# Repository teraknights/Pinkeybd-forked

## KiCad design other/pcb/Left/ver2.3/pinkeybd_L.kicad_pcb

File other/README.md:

# Pinkeybd
"Pinkeybd" is a portable wireless split keyboard with trackball

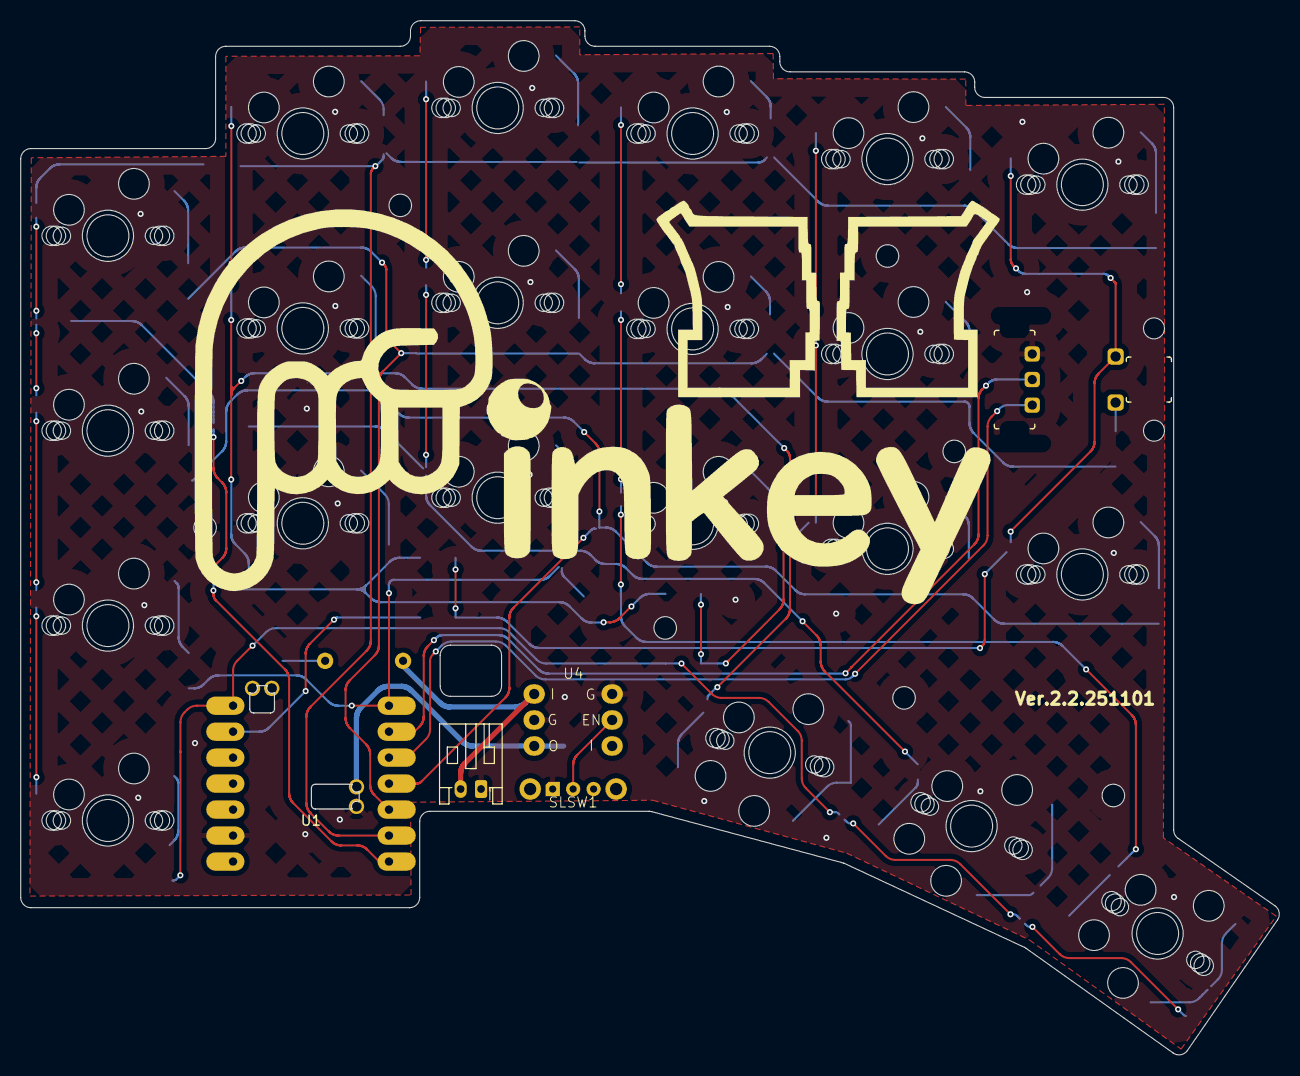
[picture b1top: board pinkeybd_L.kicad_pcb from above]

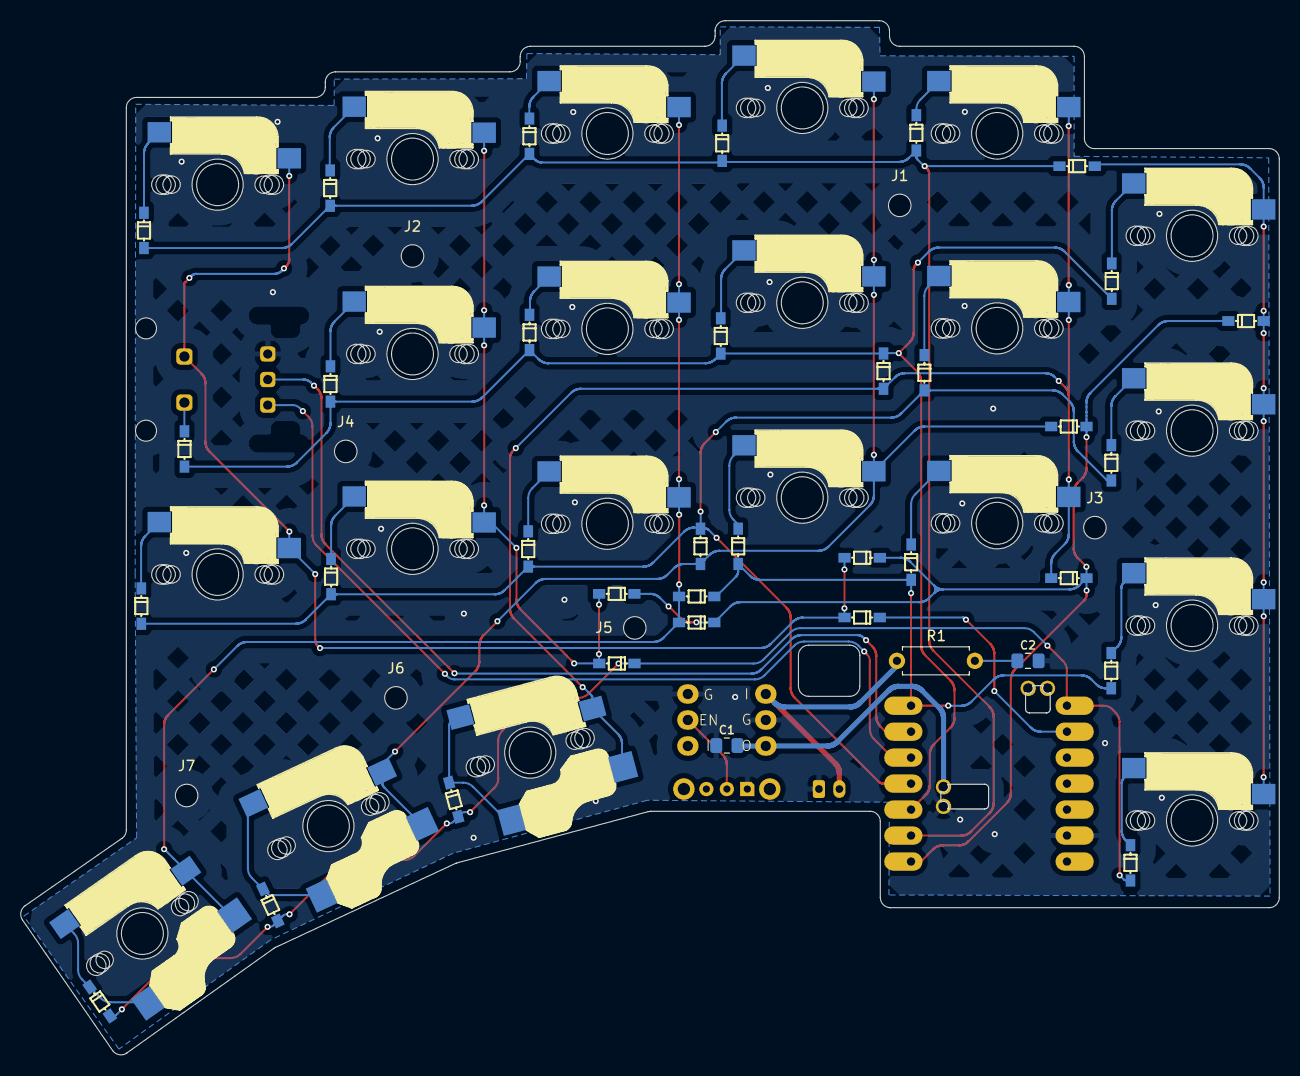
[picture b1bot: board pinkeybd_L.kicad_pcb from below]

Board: 2 copper layers, 123.0 x 101.0 mm, 68 parts (3 on the bottom side), 39 nets.

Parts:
C1: 47μF; C_0805_2012Metric_Pad1.18x1.45mm_HandSolder
C2: 1μF; C_0805_2012Metric_Pad1.18x1.45mm_HandSolder
D01, D02, D03, D04, D05, D10, D12, D13, D14, D15, D20, D21, D23, D24, D25, D30, D31, D32, D40, D41, D42, D43: 1N4148; Diode_SMD
DI1, DI2, DI3, DI4, DI5, DI6: 1N4148; Diode_SMD
DS1, DS2, DS3, DS4, DS5, DS6: 1N4148; Diode_SMD
J1, J2, J3, J4, J5, J6, J7: MountingHole_2.2mm_M2_DIN965
R1: 1M; R_Axial_DIN0207_L6.3mm_D2.5mm_P7.62mm_Horizontal
SLSW1: SK-12D11VG3; SW_Slide_SK-12D11VG3
SW: SW_PUSH; SW_MX
SW#2, SW#3, SW#4, SW#5, SW#6, SW#7, SW#8, SW#9, SW#10, SW#12, SW#13, SW#14, SW#15, SW#16, SW#17, SW#20, SW#21: SW_PUSH; SW_MX
SW#11, SW#18, SW#19: SW_PUSH; SW_MX_Choc
U1: XIAO_nRF52840_wBAT_wNFC_1
U4: DC/DC_Converter_XCL103; DC_DC_Converter_XCL103

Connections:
Bat: R1.1, U4.4
EN: SLSW1.2, U4.2
GND: C1.1, C2.2, SLSW1.1, U1.13 (GND), U1.21 (BATT-), U4.3, U4.5
INTR: DI1.1 (K), DI2.1 (K), DI3.1 (K), DI4.1 (K), DI5.1 (K), DI6.1 (K), U1.1 (P0.02_A0_D0)
IO1: D01.2 (A), D02.2 (A), D03.2 (A), D04.2 (A), D05.2 (A), DS1.1 (K), U1.2 (P0.03_A1_D1)
IO2: D10.2 (A), D12.2 (A), D13.2 (A), D14.2 (A), D15.2 (A), DS2.1 (K), U1.3 (P0.28_A2_D2)
IO3: D20.2 (A), D21.2 (A), D23.2 (A), D24.2 (A), D25.2 (A), DS3.1 (K), U1.4 (P0.29_A3_D3)
IO4: D30.2 (A), D31.2 (A), D32.2 (A), DS4.1 (K), U1.7 (P1.11_D6_TX)
IO5: D40.2 (A), D41.2 (A), D42.2 (A), D43.2 (A), DS5.1 (K), U1.8 (P1.12_D7_RX)
IO6: DS6.1 (K), U1.9 (P1.13_D8_SCK)
unnamed: C2.1, R1.2
unnamed: D01.1 (K), SW#2.2
unnamed: D02.1 (K), SW#21.2
unnamed: D03.1 (K), SW#7.2
unnamed: D04.1 (K), SW.2
unnamed: D05.1 (K), SW#9.2
unnamed: D10.1 (K), SW#4.2
unnamed: D12.1 (K), SW#15.2
unnamed: D13.1 (K), SW#13.2
unnamed: D14.1 (K), SW#12.2
unnamed: D20.1 (K), SW#17.2
unnamed: D21.1 (K), SW#14.2
unnamed: D23.1 (K), SW#6.2
unnamed: D24.1 (K), SW#10.2
unnamed: D25.1 (K), SW#8.2
unnamed: D30.1 (K), SW#16.2
unnamed: D31.1 (K), SW#5.2
unnamed: D32.1 (K), SW#3.2
unnamed: D40.1 (K), SW#20.2
unnamed: D41.1 (K), SW#11.2
unnamed: D42.1 (K), SW#18.2
unnamed: D43.1 (K), SW#19.2
unnamed: DI1.2 (A), DS1.2 (A), SW#4.1, SW#16.1, SW#17.1, SW#20.1
unnamed: DI2.2 (A), DS2.2 (A), SW#2.1, SW#5.1, SW#11.1, SW#14.1
unnamed: DI3.2 (A), DS3.2 (A), SW#3.1, SW#15.1, SW#18.1, SW#21.1
unnamed: DI4.2 (A), DS4.2 (A), SW#6.1, SW#7.1, SW#13.1, SW#19.1
unnamed: DI5.2 (A), DS5.2 (A), SW.1, SW#10.1, SW#12.1
unnamed: DI6.2 (A), DS6.2 (A), SW#8.1, SW#9.1
Vout: C1.2, U1.20 (BATT+), U4.6

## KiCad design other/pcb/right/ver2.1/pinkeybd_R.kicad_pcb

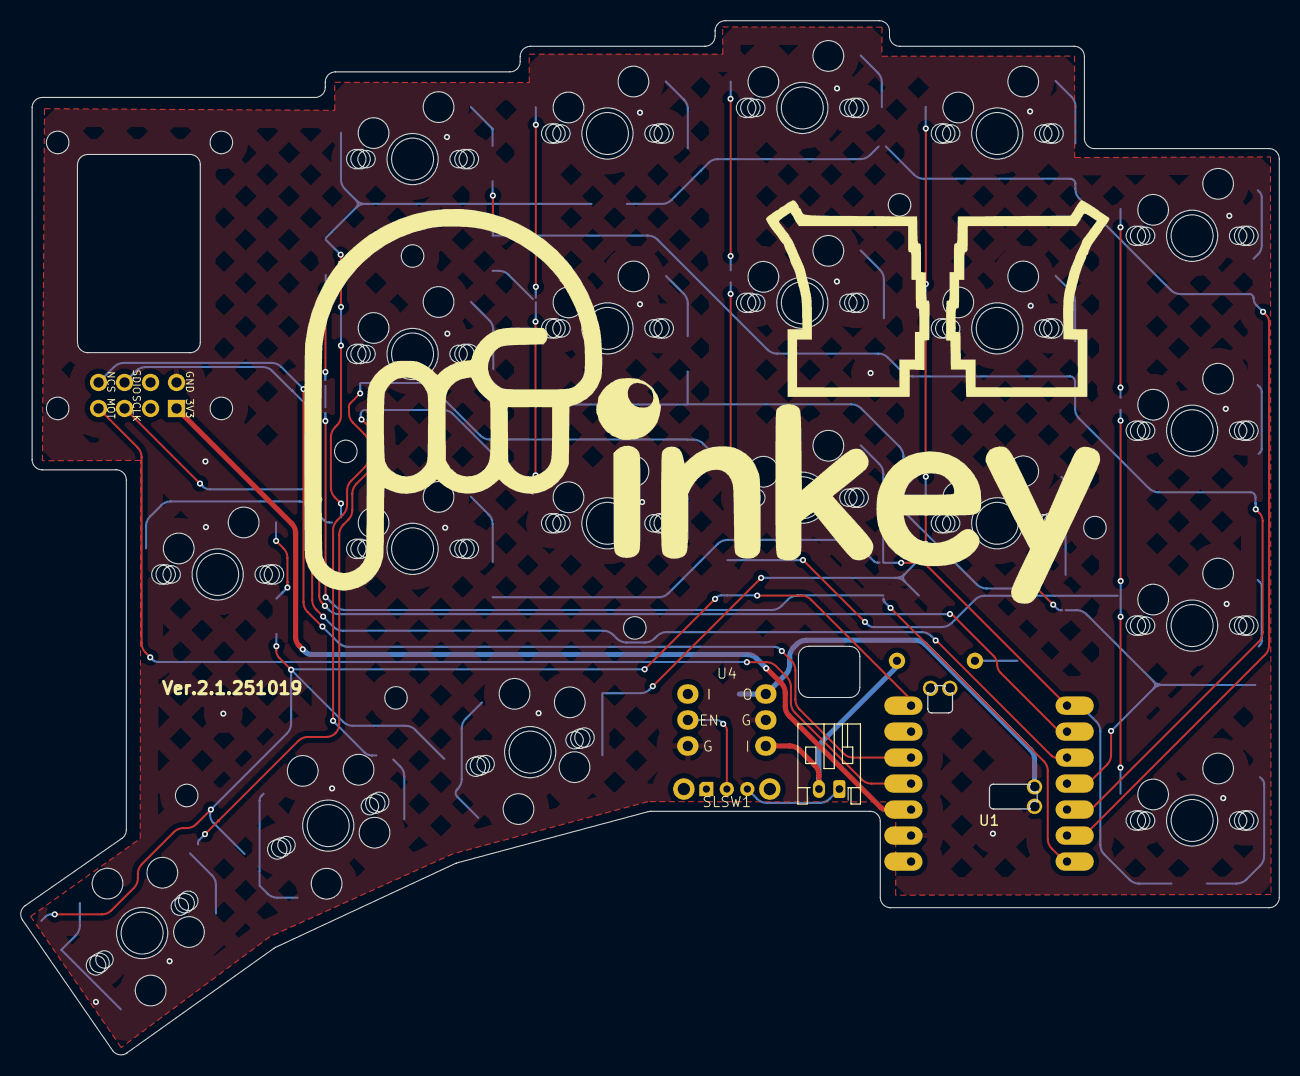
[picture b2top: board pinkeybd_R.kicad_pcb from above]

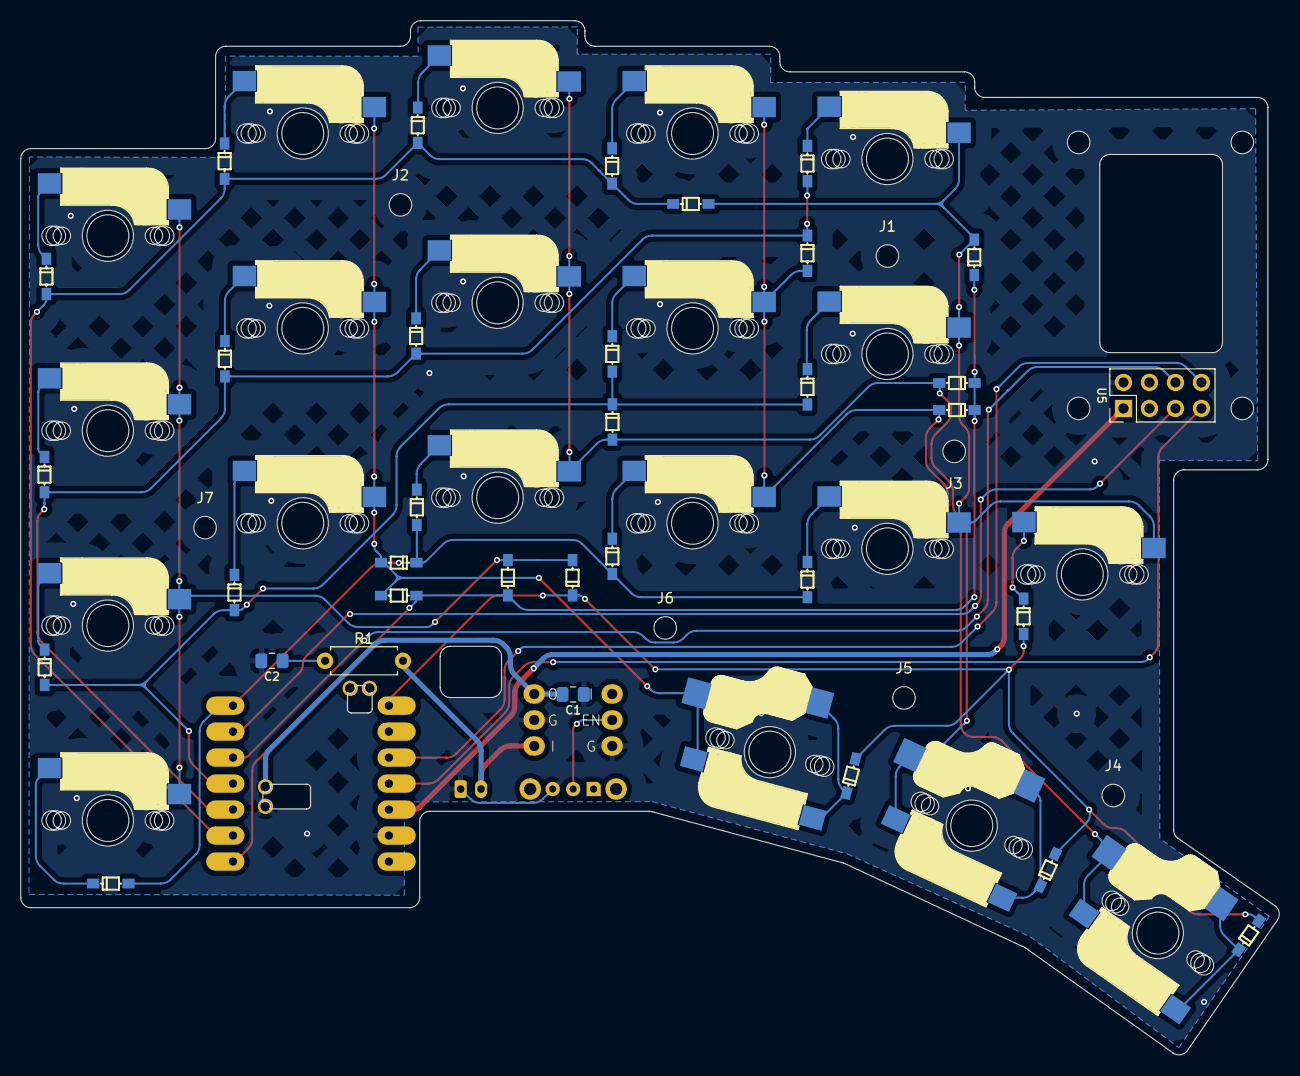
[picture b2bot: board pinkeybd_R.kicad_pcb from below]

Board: 2 copper layers, 123.0 x 101.0 mm, 68 parts (8 on the bottom side), 41 nets.

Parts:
C1: 47μF; C_0805_2012Metric_Pad1.18x1.45mm_HandSolder
C2: 1μF; C_0805_2012Metric_Pad1.18x1.45mm_HandSolder
D61, D62, D63, D64, D70, D72, D73, D74, D80, D81, D83, D84, D90, D91, D92, D94: 1N4148; Diode_SMD
DA0, DA1, DA2, DA3: 1N4148; Diode_SMD
DI7, DI8, DI9, DI10, DI11: 1N4148; Diode_SMD
DS7, DS8, DS9, DS10, DS11: 1N4148; Diode_SMD
H1, H2, H3, H4: MountingHole; MountingHole_2.2mm_M2_DIN965
J1, J2, J3, J4, J5, J6, J7: Conn_01x01-Connector_Generic; MountingHole_2.2mm_M2_DIN965
R1: 1M; R_Axial_DIN0207_L6.3mm_D2.5mm_P7.62mm_Horizontal
SLSW1: SK-12D11VG3; SW_Slide_SK-12D11VG3
SW: SW_PUSH; SW_MX
SW#2, SW#3, SW#4, SW#5, SW#6, SW#7, SW#9, SW#10, SW#11, SW#12, SW#14, SW#15, SW#16, SW#17, SW#18, SW#20: SW_PUSH; SW_MX
SW#8, SW#13, SW#19: SW_PUSH; SW_MX_Choc
U1: XIAO_nRF52840_wBAT_wNFC_1
U4: DC_DC_Converter_XCL103
U5: Conn_02x04_Odd_Even; PinHeader_2x04_P2.54mm_Vertical

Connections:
3.3V: U1.12 (3V3), U5.1
Bat: R1.1, U4.4 (IN)
EN: SLSW1.2, U4.2 (EN)
GND: C1.1, C2.2, SLSW1.3, U1.13 (GND), U1.21 (BATT-), U4.3 (GND), U4.5 (GND), U5.2
INTR: DI7.1 (K), DI8.1 (K), DI9.1 (K), DI10.1 (K), DI11.1 (K), U1.1 (P0.02_A0_D0)
IO1: D61.2 (A), D62.2 (A), D63.2 (A), D64.2 (A), DS7.1 (K), U1.2 (P0.03_A1_D1)
IO2: D70.2 (A), D72.2 (A), D73.2 (A), D74.2 (A), DS8.1 (K), U1.3 (P0.28_A2_D2)
IO3: D80.2 (A), D81.2 (A), D83.2 (A), D84.2 (A), DS9.1 (K), U1.4 (P0.29_A3_D3)
IO4: D90.2 (A), D91.2 (A), D92.2 (A), D94.2 (A), DS10.1 (K), U1.7 (P1.11_D6_TX)
IO5: DA0.2 (A), DA1.2 (A), DA2.2 (A), DA3.2 (A), DS11.1 (K), U1.8 (P1.12_D7_RX)
MOTION: U1.11 (P1.15_D10_MOSI), U5.7
NCS: U1.10 (P1.14_D9_MISO), U5.8
unnamed: C2.1, R1.2
unnamed: D61.1 (K), SW#6.2
unnamed: D62.1 (K), SW#18.2
unnamed: D63.1 (K), SW#17.2
unnamed: D64.1 (K), SW.2
unnamed: D70.1 (K), SW#12.2
unnamed: D72.1 (K), SW#15.2
unnamed: D73.1 (K), SW#16.2
unnamed: D74.1 (K), SW#3.2
unnamed: D80.1 (K), SW#5.2
unnamed: D81.1 (K), SW#7.2
unnamed: D83.1 (K), SW#20.2
unnamed: D84.1 (K), SW#11.2
unnamed: D90.1 (K), SW#9.2
unnamed: D91.1 (K), SW#10.2
unnamed: D92.1 (K), SW#14.2
unnamed: D94.1 (K), SW#2.2
unnamed: DA0.1 (K), SW#4.2
unnamed: DA1.1 (K), SW#19.2
unnamed: DA2.1 (K), SW#13.2
unnamed: DA3.1 (K), SW#8.2
unnamed: DI7.2 (A), DS7.2 (A), SW#4.1, SW#5.1, SW#9.1, SW#12.1
unnamed: DI8.2 (A), DS8.2 (A), SW#6.1, SW#7.1, SW#10.1, SW#19.1
unnamed: DI9.2 (A), DS9.2 (A), SW#13.1, SW#14.1, SW#15.1, SW#18.1
unnamed: DI10.2 (A), DS10.2 (A), SW#8.1, SW#16.1, SW#17.1, SW#20.1
unnamed: DI11.2 (A), DS11.2 (A), SW.1, SW#2.1, SW#3.1, SW#11.1
SCLK: U1.6 (P0.05_A5_D5_SCL), U5.5
SDIO: U1.5 (P0.04_A4_D4_SDA), U5.6
Vout: C1.2, U1.20 (BATT+), U4.6 (OUT)

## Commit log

2026-01-10 Add Pinkeybd (XIAO BLE) ZMK build configuration
2026-01-10 Ignore .DS_Store
2026-01-11 add setting reset
